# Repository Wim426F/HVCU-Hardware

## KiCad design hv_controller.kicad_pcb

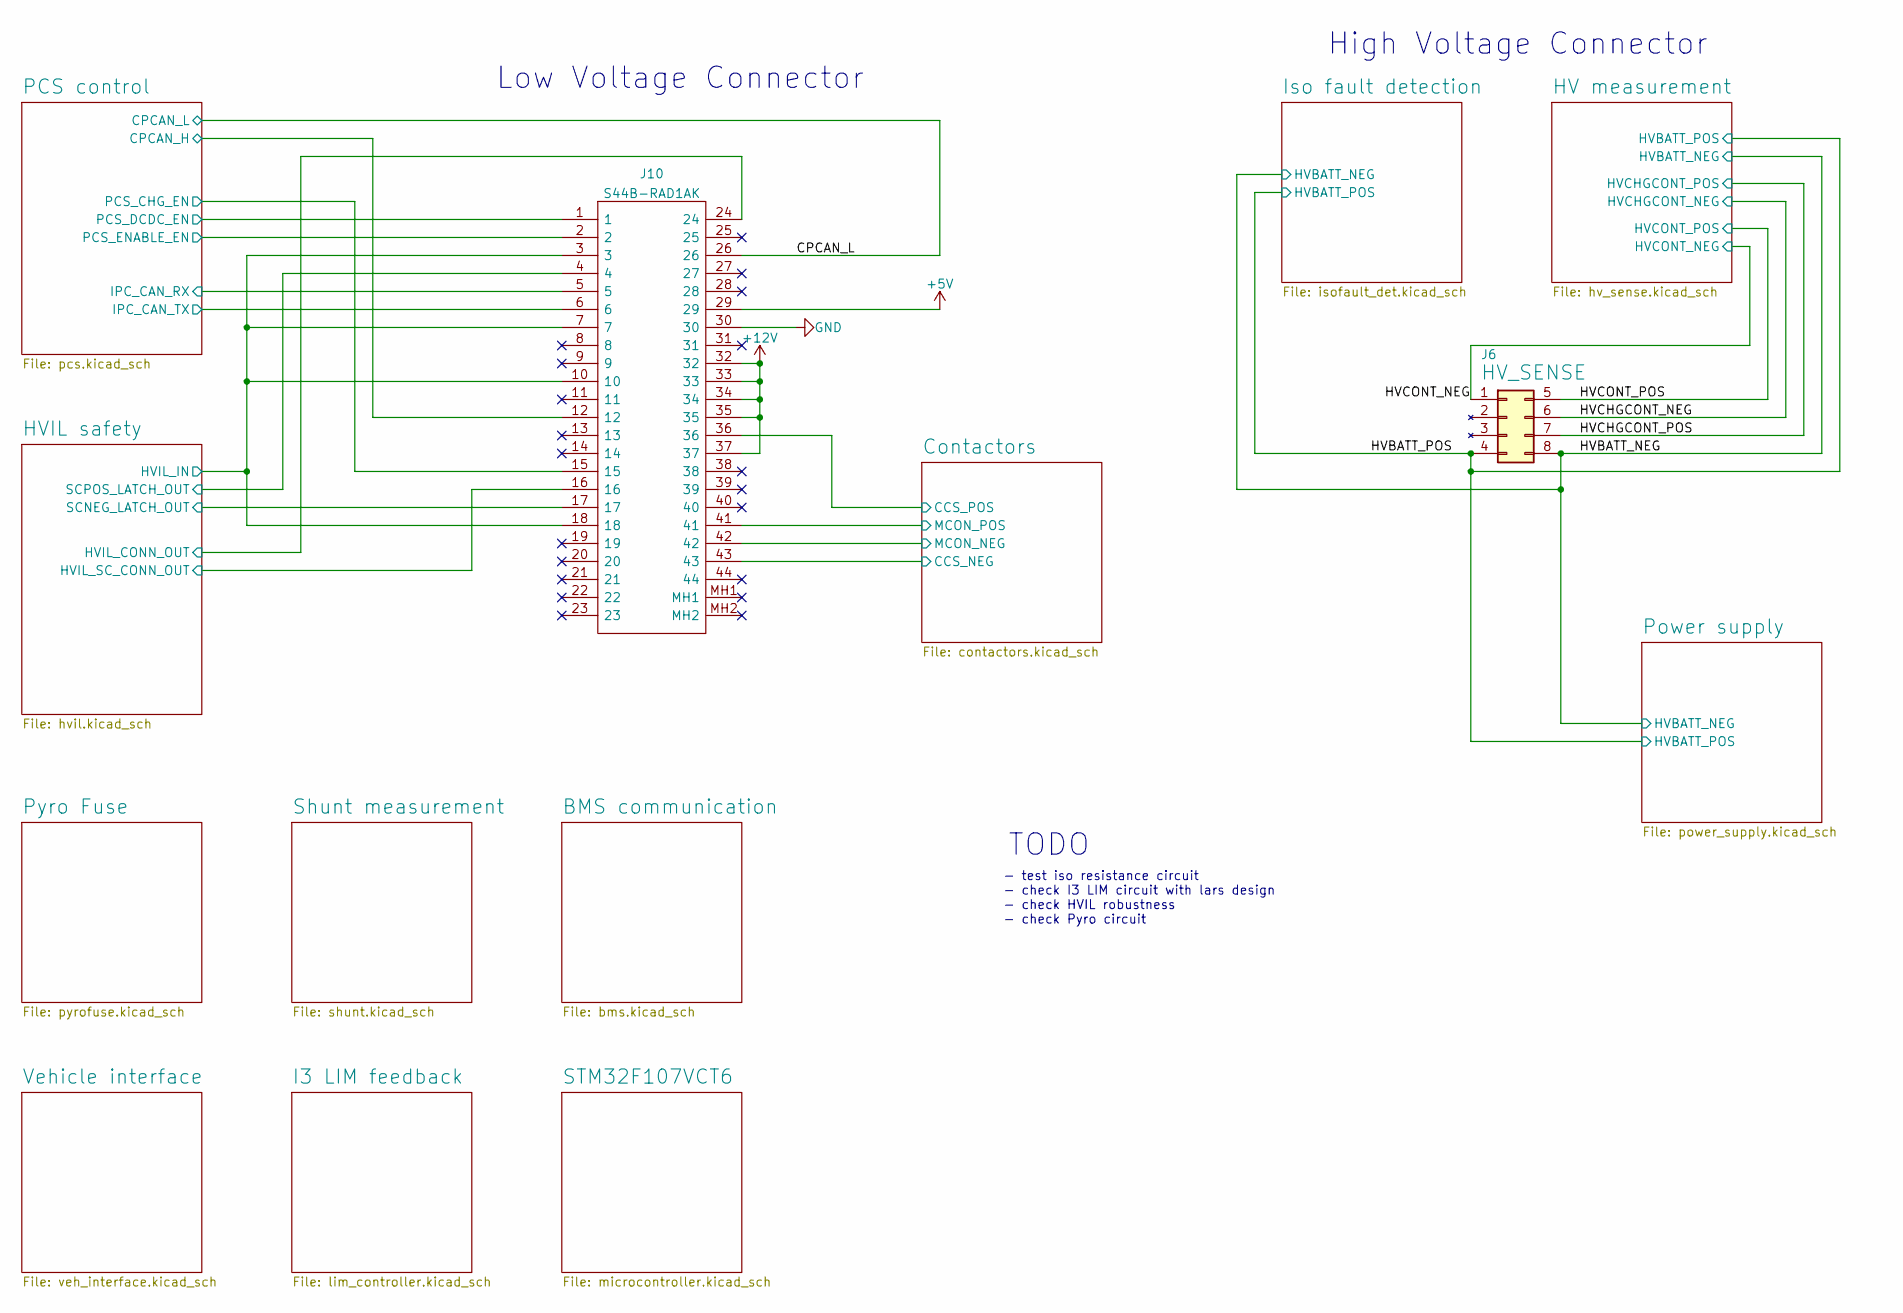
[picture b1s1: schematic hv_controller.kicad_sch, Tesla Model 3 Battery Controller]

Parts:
J6: HV_SENSE; Molex_Mini-Fit_Jr_5569-08A2_2x04_P4.20mm_Horizontal
J10: S44B-RAD1AK; S44BRAD1AK; Manufacturer_Part_Number S44B-RAD1AK; Mouser Part Number 306-S44B-RAD1AK

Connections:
+5V: J10.29; also elsewhere on the board
+12V: J10.32, J10.33, J10.34, J10.35, J10.37; also elsewhere on the board
/CPCAN_H: J10.12
/CPCAN_L: J10.26
/Contactors/CCS_NEG: J10.43; also elsewhere on the board
/Contactors/CCS_POS: J10.36; also elsewhere on the board
/Contactors/MCON_NEG: J10.42; also elsewhere on the board
/Contactors/MCON_POS: J10.41; also elsewhere on the board
/HVBATT_NEG: J6.8; also elsewhere on the board
/HVBATT_POS: J6.4; also elsewhere on the board
/HVCHGCONT_NEG: J6.6; also elsewhere on the board
/HVCHGCONT_POS: J6.7; also elsewhere on the board
/HVCONT_NEG: J6.1; also elsewhere on the board
/HVCONT_POS: J6.5; also elsewhere on the board
/HVIL safety/HVIL_CONN_OUT: J10.24; also elsewhere on the board
/HVIL safety/HVIL_IN: J10.3, J10.7, J10.10, J10.18; also elsewhere on the board
/HVIL safety/HVIL_SC_CONN_OUT: J10.16; also elsewhere on the board
/HVIL safety/SCNEG_LATCH_OUT: J10.17; also elsewhere on the board
/HVIL safety/SCPOS_LATCH_OUT: J10.4; also elsewhere on the board
/PCS control/IPC_CAN_RX: J10.5; also elsewhere on the board
/PCS control/IPC_CAN_TX: J10.6; also elsewhere on the board
/PCS control/PCS_CHG_EN: J10.15; also elsewhere on the board
/PCS control/PCS_DCDC_EN: J10.1; also elsewhere on the board
/PCS control/PCS_ENABLE_EN: J10.2; also elsewhere on the board
GND: J10.30; also elsewhere on the board

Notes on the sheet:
TODO
High Voltage Connector
Low Voltage Connector
- test iso resistance circuit - check I3 LIM circuit with lars design - check HVIL robustness - check Pyro circuit

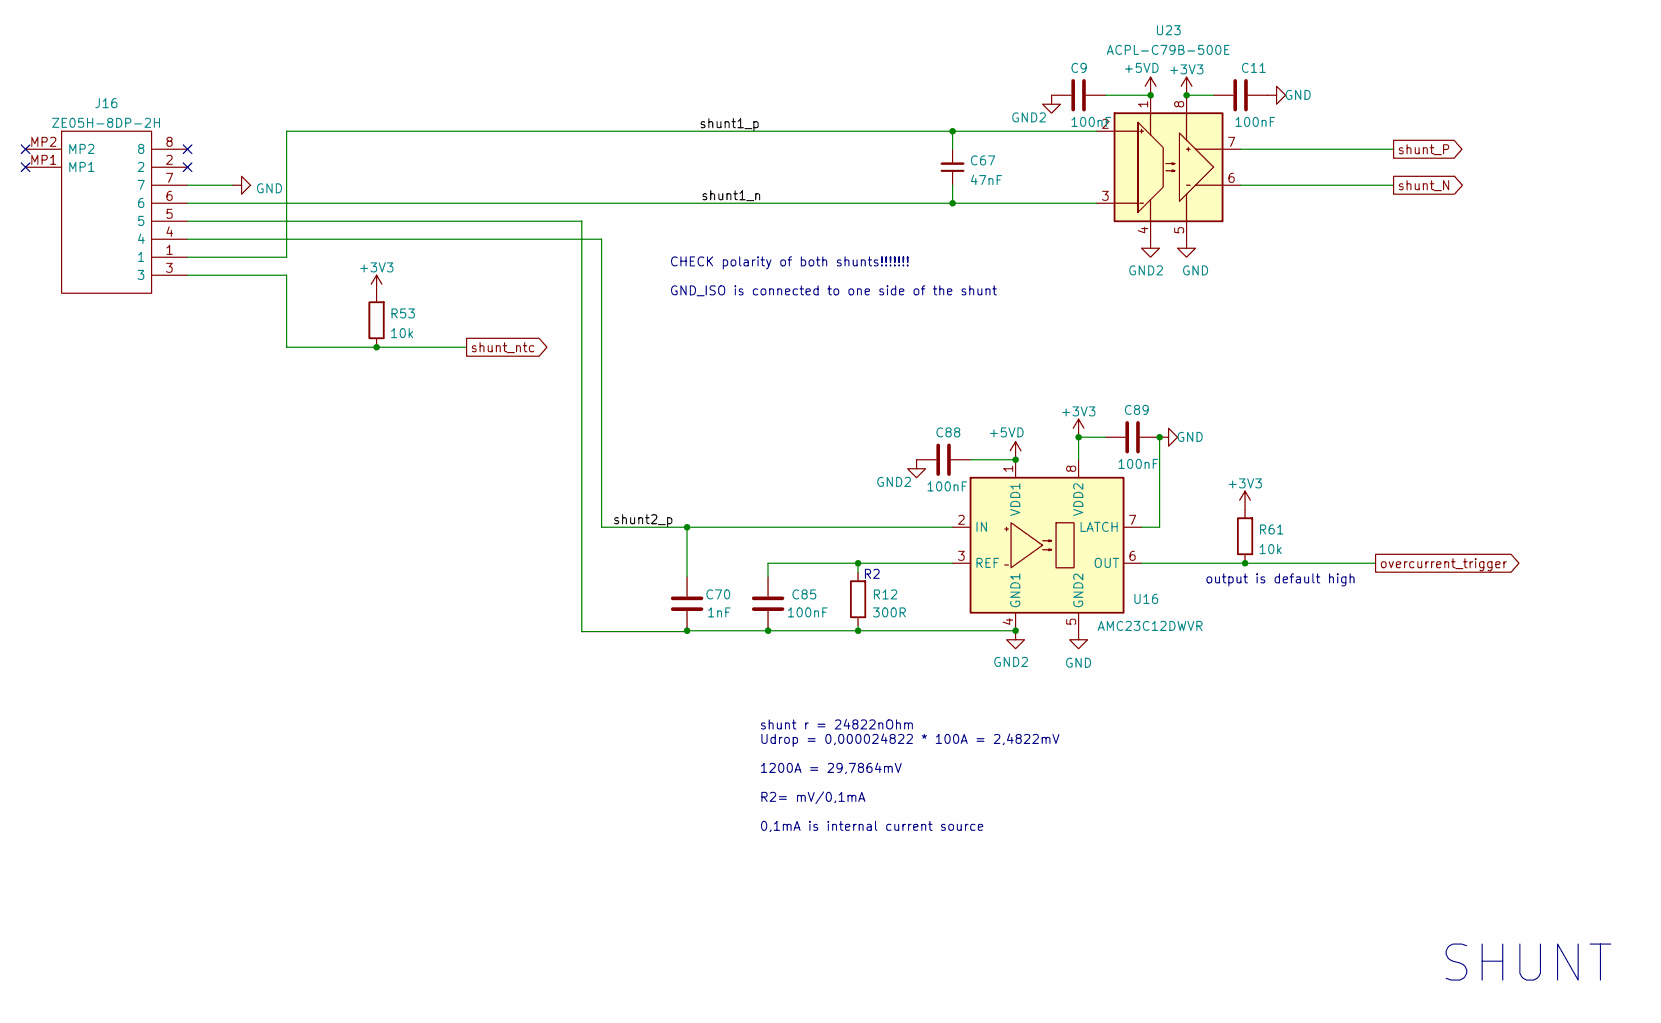
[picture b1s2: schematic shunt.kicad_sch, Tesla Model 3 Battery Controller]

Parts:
C9, C11, C85, C88, C89: 100nF; C_0603_1608Metric; LCSC Part C14663
C67: 47nF; C_0603_1608Metric; LCSC Part C1622
C70: 1nF; C_0603_1608Metric; LCSC Part C1588
J16: ZE05H-8DP-2H; ZE05H8DP2H; Manufacturer_Part_Number ZE05H-8DP-2H; Mouser Part Number 798-ZE05H-8DP-2H
R12: 300R; R_0603_1608Metric; LCSC Part C23025
R53, R61: 10k; R_0603_1608Metric; LCSC Part C25804
U16: AMC23C12DWVR; SOIC-8_7.5x5.85mm_P1.27mm; Mouser Part Number 595-AMC23C12DWVR
U23: ACPL-C79B-500E; SSO-8_6.8x5.9mm_P1.27mm_Clearance8mm; Mouser Part Number 595-AMC1300DWV; LCSC Part C691943

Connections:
+5VD: C9.1, C88.1, U16.1 (VDD1), U23.1 (VDD1); also elsewhere on the board
/Shunt measurement/shunt1_n: C67.1, J16.6, U23.3 (IN-)
/Shunt measurement/shunt1_p: C67.2, J16.1, U23.2 (IN+)
GND: C11.2, C89.2, J16.7, U16.5 (GND2), U16.7 (LATCH), U23.5 (GND2); also elsewhere on the board
unnamed: C85.2, R12.2, U16.3 (REF)
overcurrent_trigger: R61.1, U16.6 (OUT); also elsewhere on the board
shunt_N: U23.6 (OUT-); also elsewhere on the board
shunt_P: U23.7 (OUT+); also elsewhere on the board
shunt_ntc: J16.3, R53.1; also elsewhere on the board

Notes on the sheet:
SHUNT
output is default high
shunt r = 24822nOhm Udrop = 0,000024822 * 100A = 2,4822mV 1200A = 29,7864mV R2= mV/0,1mA 0,1mA is internal current source
CHECK polarity of both shunts!!!!!!! GND_ISO is connected to one side of the shunt

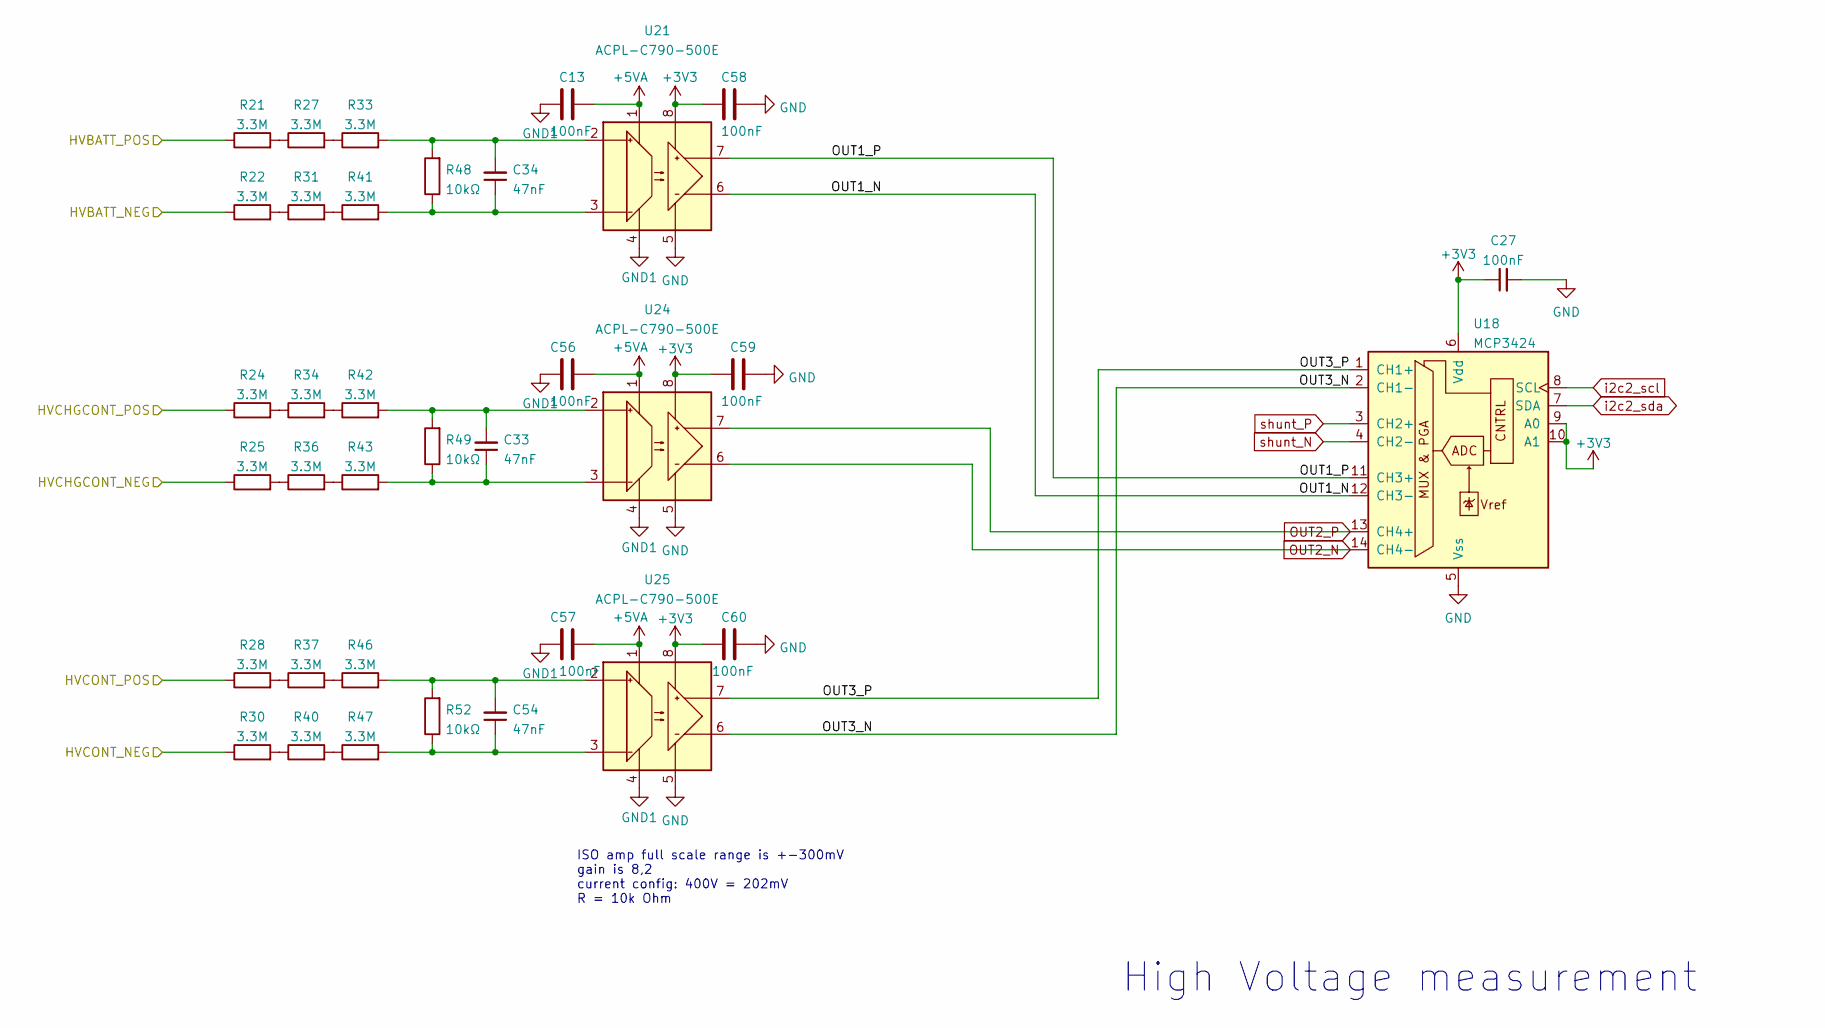
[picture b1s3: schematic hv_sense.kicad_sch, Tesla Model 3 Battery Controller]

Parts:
C13, C27, C56, C57, C58, C59, C60: 100nF; C_0603_1608Metric; LCSC Part C14663
C33, C34, C54: 47nF; C_0603_1608Metric; LCSC Part C1622
R21, R22, R24, R25, R27, R28, R30, R31, R33, R34, R36, R37, R40, R41, R42, R43, R46, R47: 3.3M; R_0805_2012Metric_Pad1.20x1.40mm_HandSolder; Manufacturer_Part_Number RG2012P-225-B-T5; Mouser Part Number 594-MCU0805MD3304BP5
R48, R49, R52: 10kΩ; R_0402_1005Metric_Pad0.72x0.64mm_HandSolder; LCSC Part C328417
U18: MCP3424; SOIC-14_3.9x8.7mm_P1.27mm; Mouser Part Number 579-MCP3424-E/SL; LCSC Part C640884
U21, U24, U25: ACPL-C790-500E; SSO-8_6.8x5.9mm_P1.27mm_Clearance8mm; Mouser Part Number 595-AMC1300DWV; LCSC Part C545687

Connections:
+5VA: C13.1, C56.1, C57.1, U21.1 (VDD1), U24.1 (VDD1), U25.1 (VDD1); also elsewhere on the board
/HV measurement/OUT1_N: U18.12 (CH3-), U21.6 (OUT-)
/HV measurement/OUT1_P: U18.11 (CH3+), U21.7 (OUT+)
/HV measurement/OUT3_N: U18.2 (CH1-), U25.6 (OUT-)
/HV measurement/OUT3_P: U18.1 (CH1+), U25.7 (OUT+)
/HVBATT_NEG: R22.1; also elsewhere on the board
/HVBATT_POS: R21.1; also elsewhere on the board
/HVCHGCONT_NEG: R25.1; also elsewhere on the board
/HVCHGCONT_POS: R24.1; also elsewhere on the board
/HVCONT_NEG: R30.1; also elsewhere on the board
/HVCONT_POS: R28.1; also elsewhere on the board
GND: C27.2, C58.1, C59.1, C60.1, U18.5 (Vss), U21.5 (GND2), U24.5 (GND2), U25.5 (GND2); also elsewhere on the board
GND1: C13.2, C56.2, C57.2, U21.4 (GND1), U24.4 (GND1), U25.4 (GND1); also elsewhere on the board
unnamed: R21.2, R27.1
unnamed: R22.2, R31.1
unnamed: R24.2, R34.1
unnamed: R25.2, R36.1
unnamed: R27.2, R33.1
unnamed: R28.2, R37.1
unnamed: R30.2, R40.1
unnamed: R31.2, R41.1
unnamed: R34.2, R42.1
unnamed: R36.2, R43.1
unnamed: R37.2, R46.1
unnamed: R40.2, R47.1
unnamed: C34.2, R33.2, R48.2, U21.2 (IN+)
unnamed: C34.1, R41.2, R48.1, U21.3 (IN-)
unnamed: C33.2, R42.2, R49.2, U24.2 (IN+)
unnamed: C33.1, R43.2, R49.1, U24.3 (IN-)
unnamed: C54.2, R46.2, R52.2, U25.2 (IN+)
unnamed: C54.1, R47.2, R52.1, U25.3 (IN-)
OUT2_N: U18.14 (CH4-), U24.6 (OUT-); also elsewhere on the board
OUT2_P: U18.13 (CH4+), U24.7 (OUT+); also elsewhere on the board
i2c2_scl: U18.8 (SCL); also elsewhere on the board
i2c2_sda: U18.7 (SDA); also elsewhere on the board
shunt_N: U18.4 (CH2-); also elsewhere on the board
shunt_P: U18.3 (CH2+); also elsewhere on the board

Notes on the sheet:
High Voltage measurement
ISO amp full scale range is +-300mV gain is 8,2 current config: 400V = 202mV R = 10k Ohm

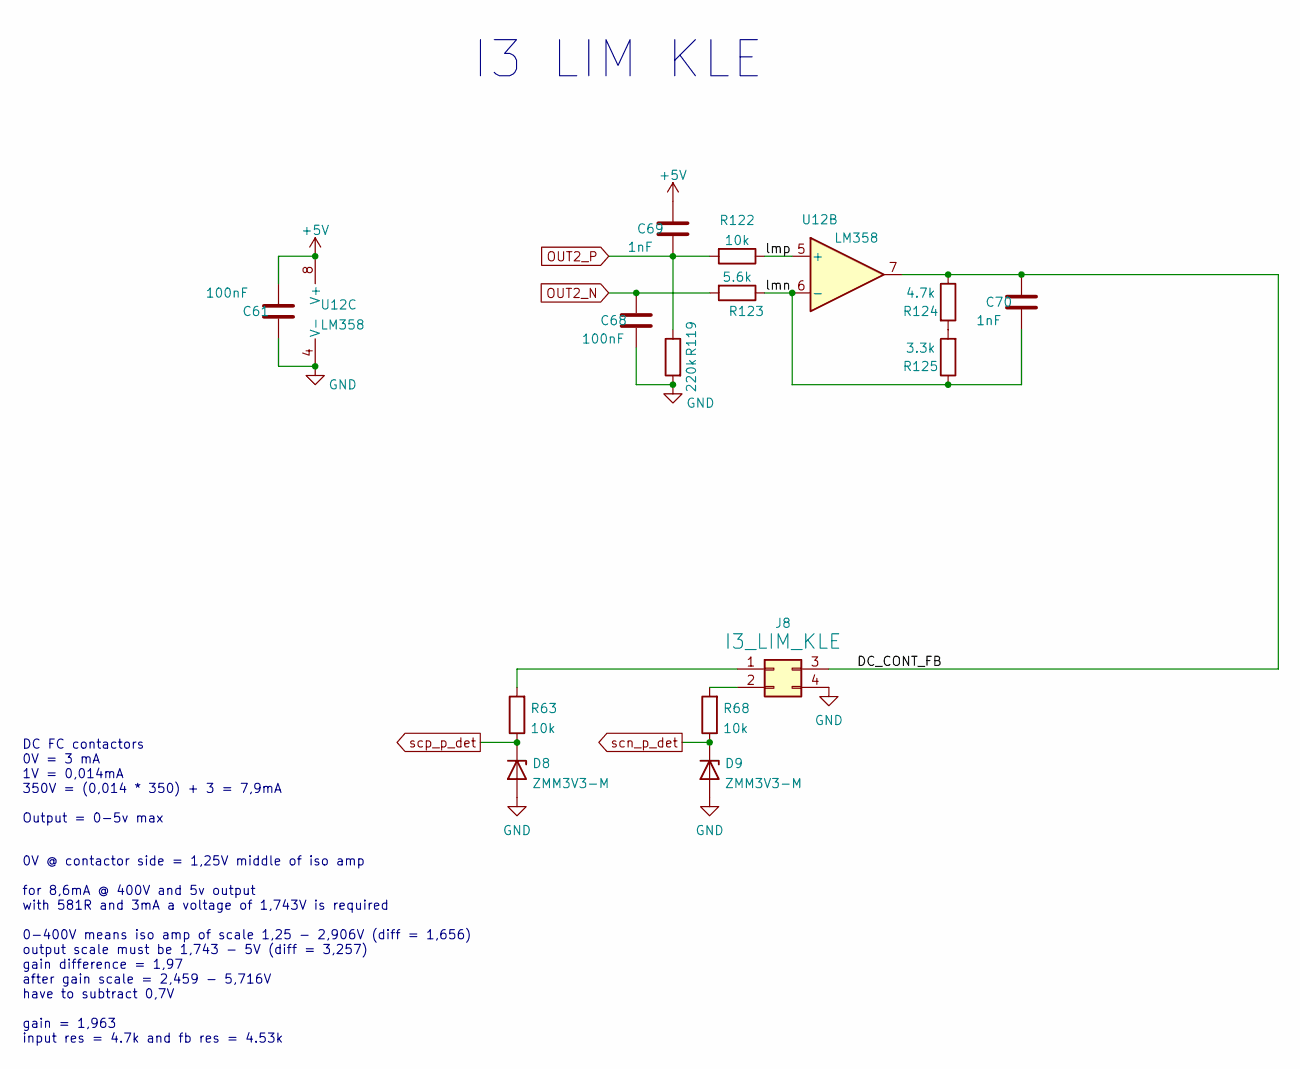
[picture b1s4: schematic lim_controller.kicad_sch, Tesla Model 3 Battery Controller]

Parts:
C61, C68: 100nF; C_0603_1608Metric; LCSC Part C14663
C69, C70: 1nF; C_0603_1608Metric; LCSC Part C1588
D8, D9: ZMM3V3-M; D_MiniMELF; LCSC Part C8056
J8: I3_LIM_KLE; Molex_MiniFit-JR-5569-04A2_2x02x4.20mm_Angled; Mouser Part Number 538-26-01-3115
R63, R68, R122: 10k; R_0603_1608Metric; LCSC Part C25804
R119: 220k; R_0603_1608Metric; LCSC Part C22961
R123: 5.6k; R_0603_1608Metric; LCSC Part C23189
R124: 4.7k; R_0603_1608Metric; LCSC Part C23162
R125: 3.3k; R_0603_1608Metric; LCSC Part C22978
U12: LM358; SOIC-8_3.9x4.9mm_P1.27mm; LCSC Part C7950

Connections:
+5V: C61.1, C69.1, U12.8 (V+); also elsewhere on the board
/I3 LIM feedback/lmp: R122.1, U12.5 (+)
GND: C61.2, C68.2, D8.2 (A), D9.2 (A), J8.4, R119.2, U12.4 (V-); also elsewhere on the board
unnamed: J8.1, R63.2
unnamed: J8.2, R68.2
unnamed: R124.2, R125.2
OUT2_N: C68.1, R123.2; also elsewhere on the board
OUT2_P: C69.2, R119.1, R122.2; also elsewhere on the board
scn_p_det: D9.1 (K), R68.1; also elsewhere on the board
scp_p_det: D8.1 (K), R63.1; also elsewhere on the board

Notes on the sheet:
0V @ contactor side = 1,25V middle of iso amp for 8,6mA @ 400V and 5v output with 581R and 3mA a voltage of 1,743V is required 0-400V means iso amp of scale 1,25 - 2,906V (diff = 1,656) output scale must be 1,743 - 5V (diff = 3,257) gain difference = 1,97 after gain scale = 2,459 - 5,716V have to s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
DC FC contactors 0V = 3 mA 1V = 0,014mA 350V = (0,014 * 350) + 3 = 7,9mA Output = 0-5v max
I3 LIM KLE

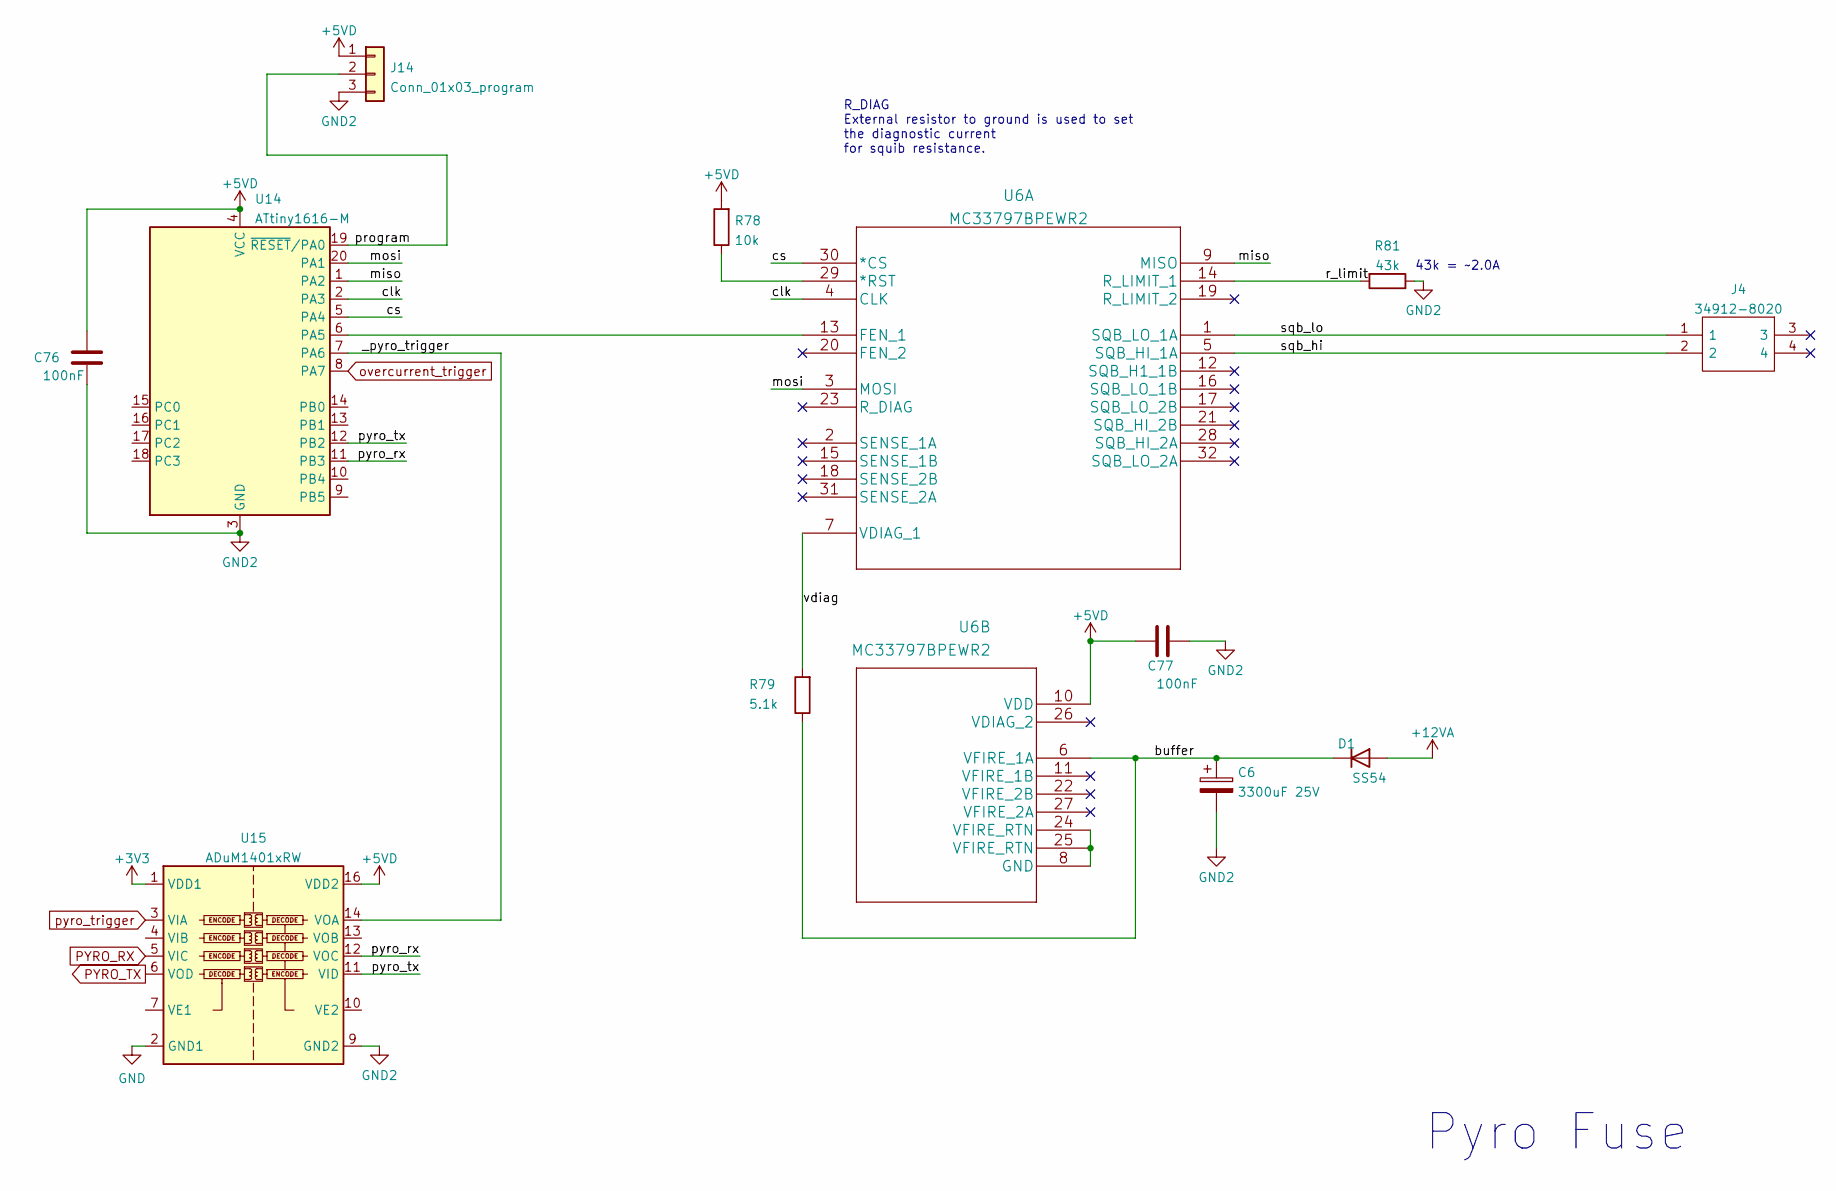
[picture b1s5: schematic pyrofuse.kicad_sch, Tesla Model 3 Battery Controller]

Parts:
C6: 3300uF 25V; CP_Radial_D16.0mm_P7.50mm; LCSC Part C442846
C76, C77: 100nF; C_0603_1608Metric; LCSC Part C14663
D1: SS54; D_SMA; LCSC Part C22452
J4: 34912-8020; 0349128020; Manufacturer_Part_Number 34912-8020; Mouser Part Number 538-34912-8022
J14: Conn_01x03_program; PinHeader_1x03_P2.54mm_Vertical
R78: 10k; R_0603_1608Metric; LCSC Part C25804
R79: 5.1k; R_0603_1608Metric; LCSC Part C23186
R81: 43k; R_0603_1608Metric; LCSC Part C445638
U6: MC33797BPEWR2; Manufacturer_Part_Number MC33797BPEWR2; LCSC Part C729196
U14: ATtiny1616-M; VQFN-20-1EP_3x3mm_P0.4mm_EP1.7x1.7mm; LCSC Part C507118
U15: ADuM1401xRW; SOIC-16W_7.5x10.3mm_P1.27mm; LCSC Part C33273

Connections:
+5VD: C76.1, C77.2, J14.1, R78.2, U6.10 (VDD), U14.4 (VCC), U15.16 (VDD2); also elsewhere on the board
+12VA: D1.2 (A); also elsewhere on the board
/Pyro Fuse/_pyro_trigger: U14.7 (PA6), U15.14 (VOA)
/Pyro Fuse/buffer: C6.1, D1.1 (K), R79.1, U6.6 (VFIRE_1A)
/Pyro Fuse/clk: U6.4 (CLK), U14.2 (PA3)
/Pyro Fuse/cs: U6.30 (*CS), U14.5 (PA4)
/Pyro Fuse/miso: U6.9 (MISO), U14.1 (PA2)
/Pyro Fuse/mosi: U6.3 (MOSI), U14.20 (PA1)
/Pyro Fuse/program: J14.2, U14.19 (~RESET/PA0)
/Pyro Fuse/pyro_rx: U14.11 (PB3), U15.12 (VOC)
/Pyro Fuse/pyro_tx: U14.12 (PB2), U15.11 (VID)
/Pyro Fuse/r_limit: R81.2, U6.14 (R_LIMIT_1)
/Pyro Fuse/sqb_hi: J4.2, U6.5 (SQB_HI_1A)
/Pyro Fuse/sqb_lo: J4.1, U6.1 (SQB_LO_1A)
/Pyro Fuse/vdiag: R79.2, U6.7 (VDIAG_1)
GND: U15.2 (GND1), U15.8 (GND1); also elsewhere on the board
unnamed: R78.1, U6.29 (*RST)
unnamed: U6.8 (GND), U6.24 (VFIRE_RTN), U6.25 (VFIRE_RTN)
unnamed: U6.13 (FEN_1), U14.6 (PA5)
PYRO_RX: U15.5 (VIC)
PYRO_TX: U15.6 (VOD)
overcurrent_trigger: U14.8 (PA7); also elsewhere on the board
pyro_trigger: U15.3 (VIA); also elsewhere on the board

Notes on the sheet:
Pyro Fuse
43k = ~2.0A
R_DIAG External resistor to ground is used to set the diagnostic current for squib resistance.

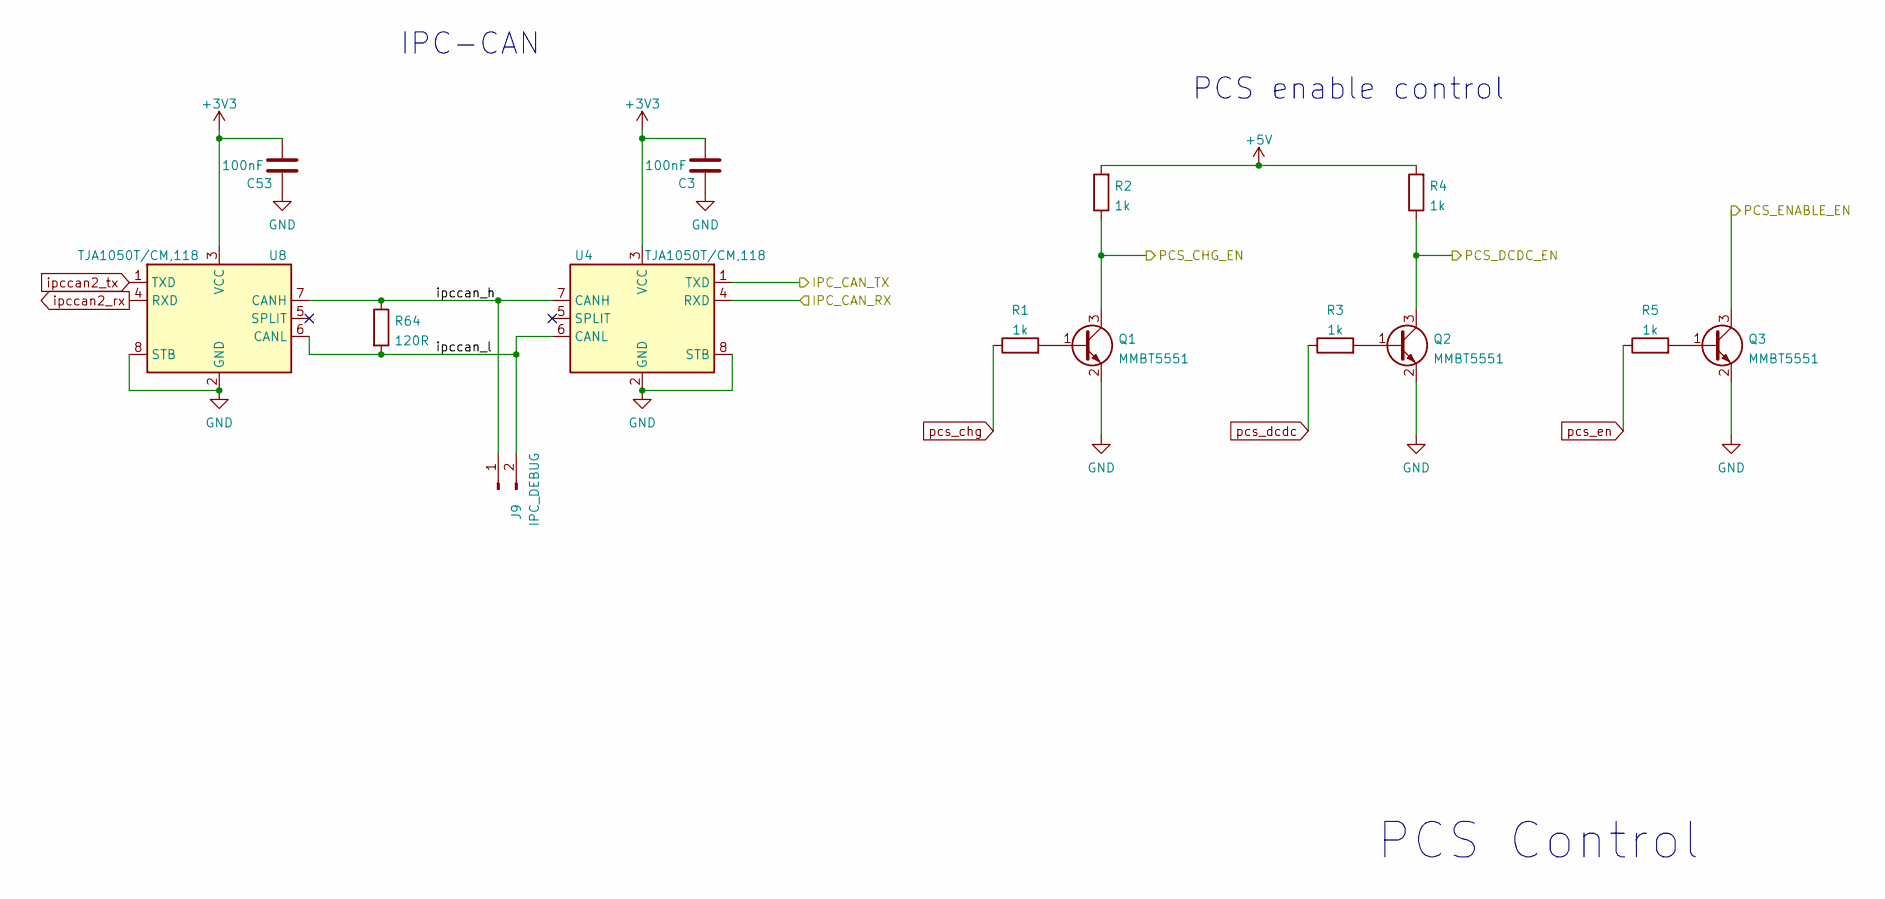
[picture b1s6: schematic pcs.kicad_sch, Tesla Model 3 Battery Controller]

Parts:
C3, C53: 100nF; C_0603_1608Metric; LCSC Part C14663
J9: IPC_DEBUG; TestPoint_2Pads_Pitch2.54mm_Drill0.8mm
Q1, Q2, Q3: MMBT5551; SOT-23; LCSC Part C2145
R1, R2, R3, R4, R5: 1k; R_0603_1608Metric; LCSC Part C21190
R64: 120R; R_0603_1608Metric; LCSC Part C22787
U4, U8: TJA1050T/CM,118; SOIC-8_3.9x4.9mm_P1.27mm; LCSC Part C6952

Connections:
+5V: R2.2, R4.2; also elsewhere on the board
/PCS control/IPC_CAN_RX: U4.4 (RXD); also elsewhere on the board
/PCS control/IPC_CAN_TX: U4.1 (TXD); also elsewhere on the board
/PCS control/PCS_CHG_EN: Q1.3 (C), R2.1; also elsewhere on the board
/PCS control/PCS_DCDC_EN: Q2.3 (C), R4.1; also elsewhere on the board
/PCS control/PCS_ENABLE_EN: Q3.3 (C); also elsewhere on the board
/PCS control/ipccan_h: J9.1, R64.1, U4.7 (CANH), U8.7 (CANH)
/PCS control/ipccan_l: J9.2, R64.2, U4.6 (CANL), U8.6 (CANL)
GND: C3.1, C53.1, Q1.2 (E), Q2.2 (E), Q3.2 (E), U4.2 (GND), U4.8 (STB), U8.2 (GND), U8.8 (STB); also elsewhere on the board
unnamed: Q1.1 (B), R1.2
unnamed: Q2.1 (B), R3.2
unnamed: Q3.1 (B), R5.2
ipccan2_rx: U8.4 (RXD); also elsewhere on the board
ipccan2_tx: U8.1 (TXD); also elsewhere on the board
pcs_chg: R1.1; also elsewhere on the board
pcs_dcdc: R3.1; also elsewhere on the board
pcs_en: R5.1; also elsewhere on the board

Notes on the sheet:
IPC-CAN
PCS enable control
PCS Control

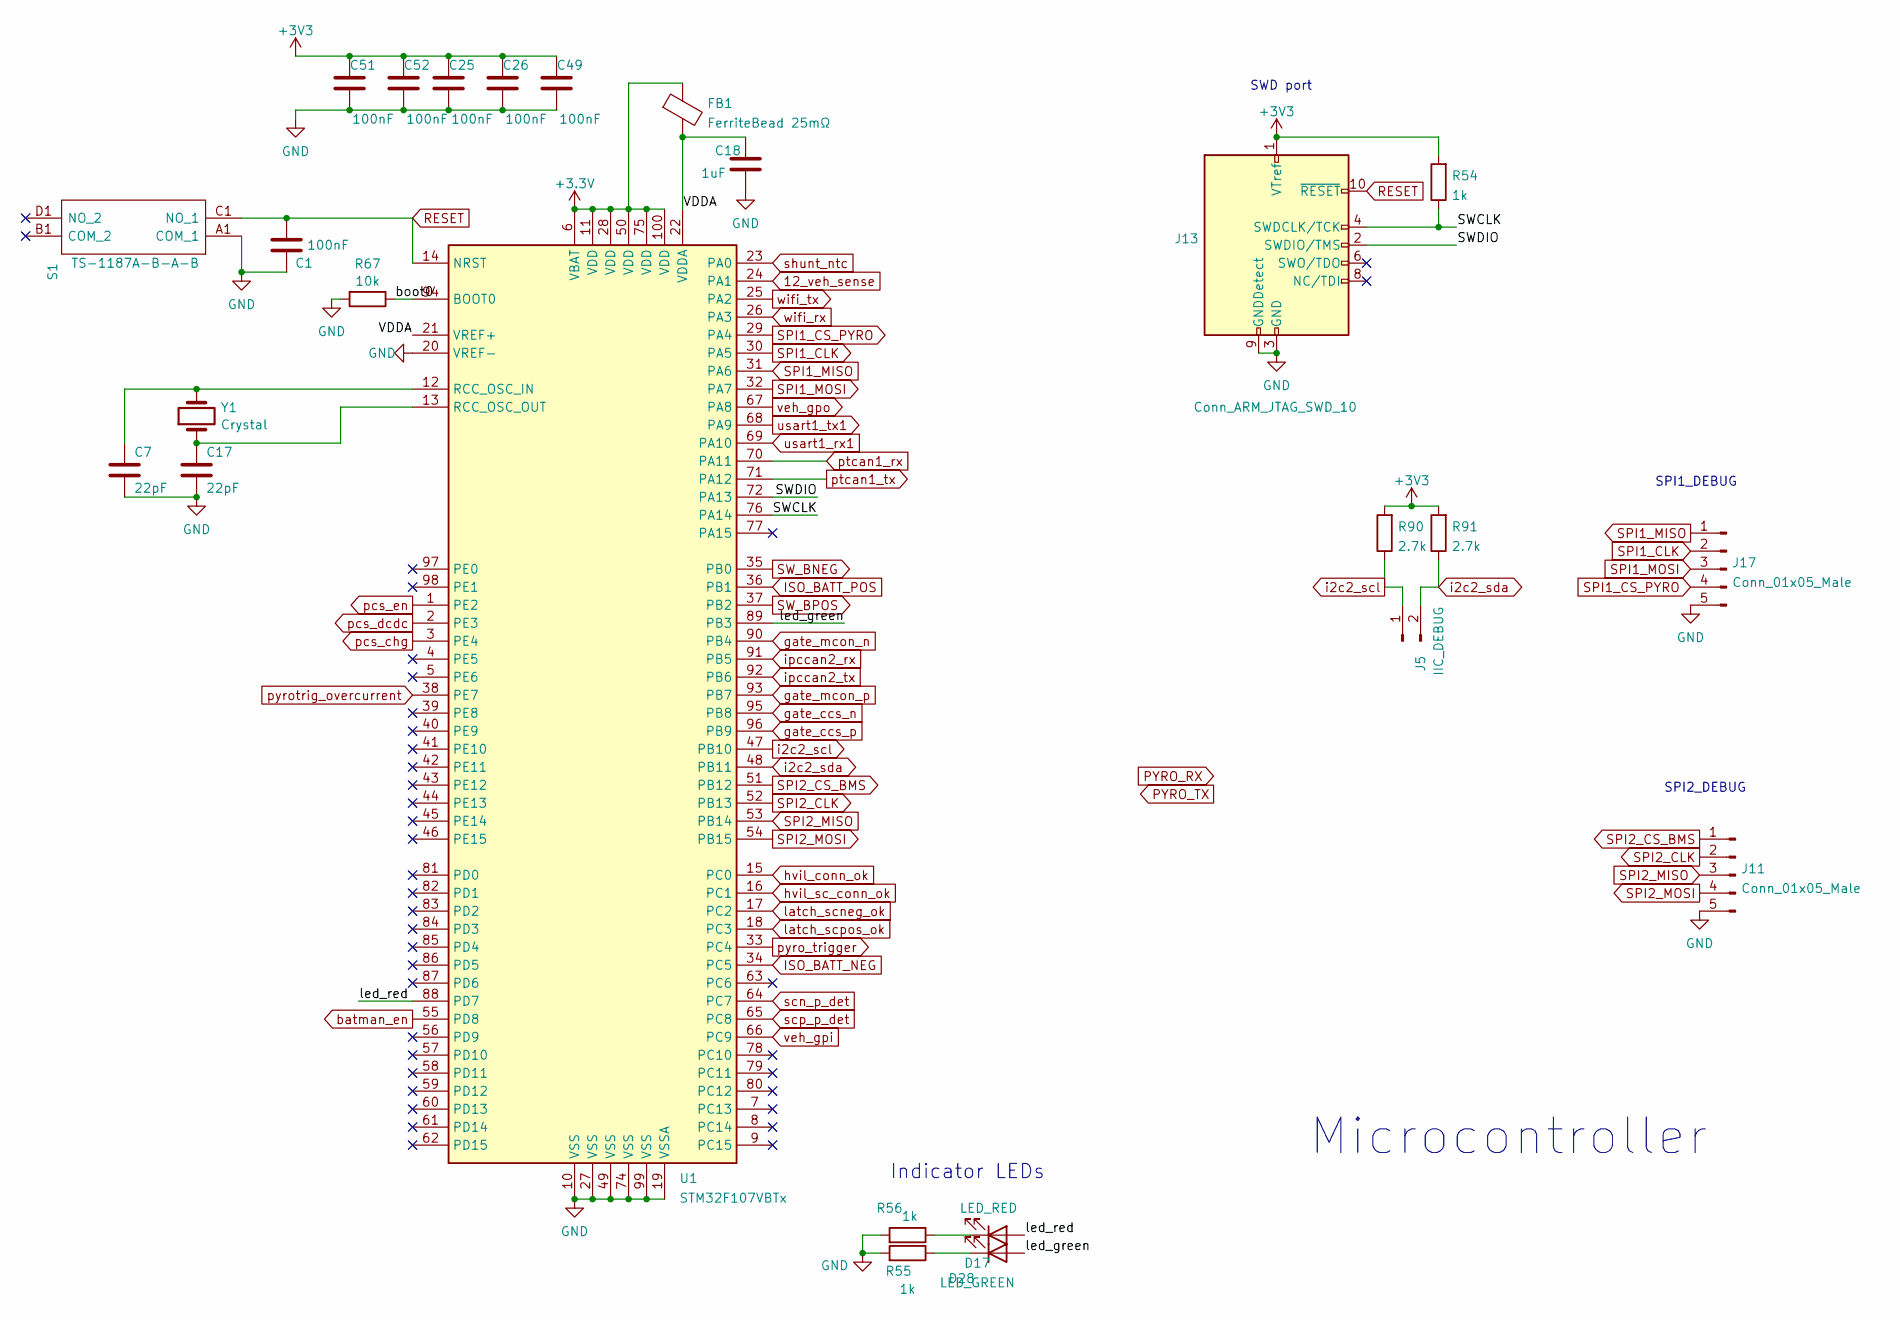
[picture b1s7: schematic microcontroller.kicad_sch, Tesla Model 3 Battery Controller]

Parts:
C1, C25, C26, C49, C51, C52: 100nF; C_0603_1608Metric; LCSC Part C14663
C7, C17: 22pF; C_0603_1608Metric; LCSC Part C1653
C18: 1uF; C_0603_1608Metric; LCSC Part C15849
D17: LED_GREEN; LED_0603_1608Metric_Pad1.05x0.95mm_HandSolder; LCSC Part C72043
D28: LED_RED; LED_0805_2012Metric_Pad1.15x1.40mm_HandSolder; LCSC Part C84256
FB1: FerriteBead 25mΩ; L_0805_2012Metric_Pad1.05x1.20mm_HandSolder; LCSC Part C840593
J5: IIC_DEBUG; TestPoint_2Pads_Pitch2.54mm_Drill0.8mm
J11, J17: Conn_01x05_Male; PinHeader_1x05_P1.27mm_Vertical
J13: Conn_ARM_JTAG_SWD_10; PinHeader_2x05_P1.27mm_JTAG_SMD
R54, R55, R56: 1k; R_0603_1608Metric; LCSC Part C21190
R67: 10k; R_0603_1608Metric; LCSC Part C25804
R90, R91: 2.7k; R_0603_1608Metric; LCSC Part C13167
S1: TS-1187A-B-A-B; TS1187ABAB; Manufacturer_Part_Number TS-1187A-B-A-B; LCSC Part C318884
U1: STM32F107VBTx; LQFP-100_14x14mm_P0.5mm
Y1: Crystal; Crystal_SMD_5032-2Pin_5.0x3.2mm; LCSC Part C115962

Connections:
12_veh_sense: U1.24 (PA1)
/STM32F107VCT6/SWCLK: J13.4 (SWDCLK/TCK), R54.1, U1.76 (PA14)
/STM32F107VCT6/SWDIO: J13.2 (SWDIO/TMS), U1.72 (PA13)
/STM32F107VCT6/VDDA: C18.1, FB1.2, U1.21 (VREF+), U1.22 (VDDA)
/STM32F107VCT6/boot0: R67.1, U1.94 (BOOT0)
/STM32F107VCT6/led_green: D17.2 (A), U1.89 (PB3)
/STM32F107VCT6/led_red: D28.2 (A), U1.88 (PD7)
GND: C1.1, C7.2, C17.2, C18.2, C25.1, C26.1, C49.1, C51.1, C52.1, J11.5, J13.3 (GND), J13.5 (GND), J13.9 (GNDDetect), J17.5, R55.2, R56.2, R67.2, S1.A1 (COM_1), U1.10 (VSS), U1.19 (VSSA), U1.20 (VREF-), U1.27 (VSS), U1.49 (VSS), U1.74 (VSS), U1.99 (VSS); also elsewhere on the board
ISO_BATT_NEG: U1.34 (PC5); also elsewhere on the board
ISO_BATT_POS: U1.36 (PB1); also elsewhere on the board
unnamed: D17.1 (K), R55.1
unnamed: D28.1 (K), R56.1
unnamed: C7.1, U1.12 (RCC_OSC_IN), Y1.2
unnamed: C17.1, U1.13 (RCC_OSC_OUT), Y1.1
RESET: C1.2, J13.10 (~RESET), S1.C1 (NO_1), U1.14 (NRST)
SPI1_CLK: J17.2, U1.30 (PA5)
SPI1_CS_PYRO: J17.4, U1.29 (PA4)
SPI1_MISO: J17.1, U1.31 (PA6)
SPI1_MOSI: J17.3, U1.32 (PA7)
SPI2_CLK: J11.2, U1.52 (PB13); also elsewhere on the board
SPI2_CS_BMS: J11.1, U1.51 (PB12); also elsewhere on the board
SPI2_MISO: J11.3, U1.53 (PB14); also elsewhere on the board
SPI2_MOSI: J11.4, U1.54 (PB15); also elsewhere on the board
SW_BNEG: U1.35 (PB0); also elsewhere on the board
SW_BPOS: U1.37 (PB2); also elsewhere on the board
batman_en: U1.55 (PD8); also elsewhere on the board
gate_ccs_n: U1.95 (PB8); also elsewhere on the board
gate_ccs_p: U1.96 (PB9); also elsewhere on the board
gate_mcon_n: U1.90 (PB4); also elsewhere on the board
gate_mcon_p: U1.93 (PB7); also elsewhere on the board
hvil_conn_ok: U1.15 (PC0); also elsewhere on the board
hvil_sc_conn_ok: U1.16 (PC1); also elsewhere on the board
i2c2_scl: J5.1, R90.1, U1.47 (PB10); also elsewhere on the board
i2c2_sda: J5.2, R91.1, U1.48 (PB11); also elsewhere on the board
ipccan2_rx: U1.91 (PB5); also elsewhere on the board
ipccan2_tx: U1.92 (PB6); also elsewhere on the board
latch_scneg_ok: U1.17 (PC2); also elsewhere on the board
latch_scpos_ok: U1.18 (PC3); also elsewhere on the board
pcs_chg: U1.3 (PE4); also elsewhere on the board
pcs_dcdc: U1.2 (PE3); also elsewhere on the board
pcs_en: U1.1 (PE2); also elsewhere on the board
ptcan1_rx: U1.70 (PA11); also elsewhere on the board
ptcan1_tx: U1.71 (PA12); also elsewhere on the board
pyro_trigger: U1.33 (PC4); also elsewhere on the board
pyrotrig_overcurrent: U1.38 (PE7)
scn_p_det: U1.64 (PC7); also elsewhere on the board
scp_p_det: U1.65 (PC8); also elsewhere on the board
shunt_ntc: U1.23 (PA0); also elsewhere on the board
usart1_rx1: U1.69 (PA10); also elsewhere on the board
usart1_tx1: U1.68 (PA9); also elsewhere on the board
veh_gpi: U1.66 (PC9); also elsewhere on the board
veh_gpo: U1.67 (PA8); also elsewhere on the board
wifi_rx: U1.26 (PA3); also elsewhere on the board
wifi_tx: U1.25 (PA2); also elsewhere on the board

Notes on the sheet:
SWD port
SPI2_DEBUG
Indicator LEDs
Microcontroller
SPI1_DEBUG

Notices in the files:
hv_controller.kicad_pcb:
©Copyright Wim Boone 2023
parts and their libraries:
Copyright 2021 Accelerated Designs. All rights reserved.
